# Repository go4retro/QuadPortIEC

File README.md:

# QuadPortIEC
Extremely simple 4 port IEC "extension" port.

This hardly qualifies as a design.  In 2010, Sean Kenny asked if I could design a simple board that allowed him to "disable" some of the drives on the IEC drive bus so he could have multiple devices with the same device number.  The design relies on the fact that an IEC device can be effectively "hidden" by interrupting the ATN line to that device.  

Feel free to use as desired.  Files are in EAGLE CAD format.

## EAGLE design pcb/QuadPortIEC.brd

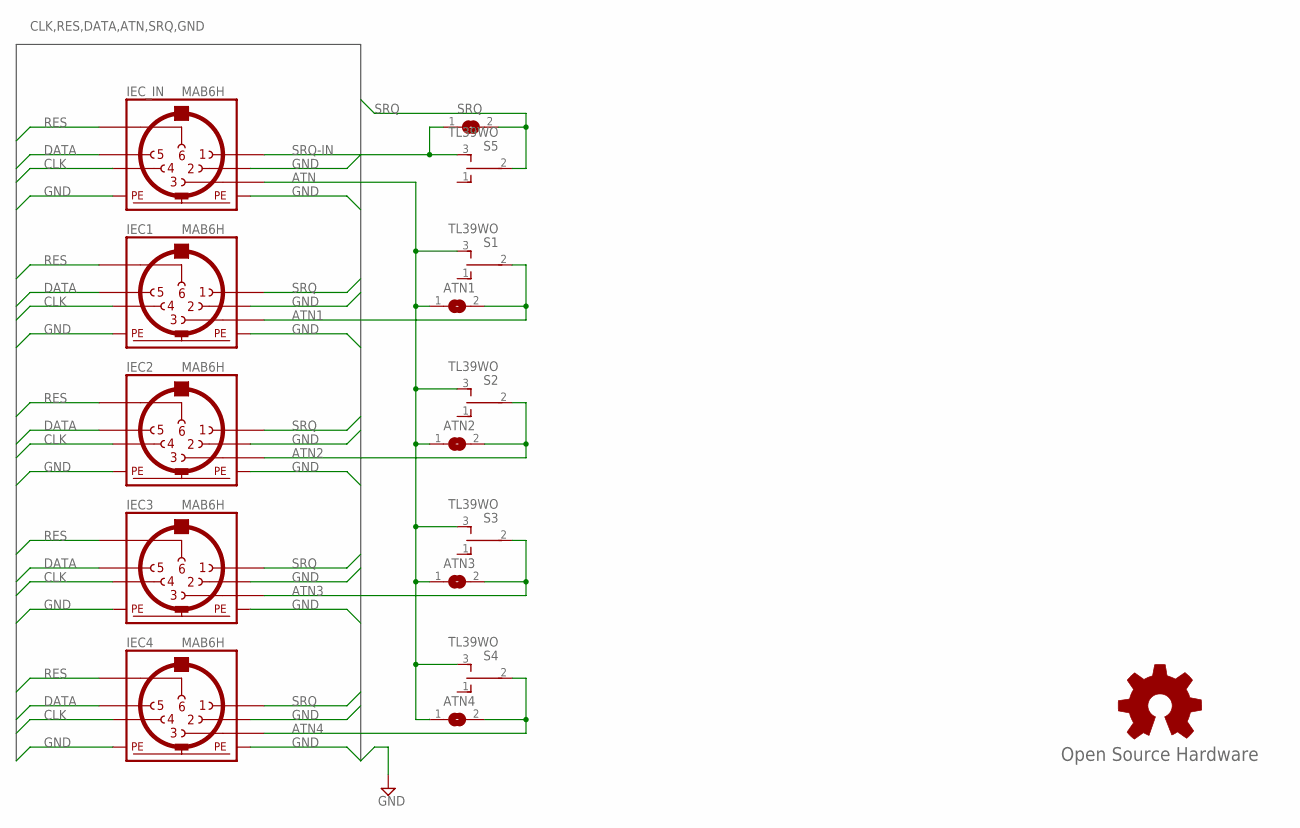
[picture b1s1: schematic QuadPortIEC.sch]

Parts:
ATN1, ATN2, ATN3, ATN4: SJ
GOLD_ORB_SM1: Open Source Hardware; OSHW_8MM
IEC1, IEC2, IEC3, IEC4: MAB6H
IEC_IN: MAB6H
S1, S2, S3, S4, S5: TL39WO; TL3XWO
SRQ: SJ

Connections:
ATN: ATN1.1, ATN2.1, ATN3.1, ATN4.1, IEC_IN.3, S1.3 (S), S2.3 (S), S3.3 (S), S4.3 (S)
ATN1: ATN1.2, IEC1.3, S1.2
ATN2: ATN2.2, IEC2.3, S2.2
ATN3: ATN3.2, IEC3.3, S3.2
ATN4: ATN4.2, IEC4.3, S4.2
CLK: IEC1.4, IEC2.4, IEC3.4, IEC4.4, IEC_IN.4
DATA: IEC1.5, IEC2.5, IEC3.5, IEC4.5, IEC_IN.5
GND: IEC1.2, IEC1.PE, IEC1.PE@ (PE), IEC2.2, IEC2.PE, IEC2.PE@ (PE), IEC3.2, IEC3.PE, IEC3.PE@ (PE), IEC4.2, IEC4.PE, IEC4.PE@ (PE), IEC_IN.2, IEC_IN.PE, IEC_IN.PE@ (PE)
RES: IEC1.6, IEC2.6, IEC3.6, IEC4.6, IEC_IN.6
SRQ: IEC1.1, IEC2.1, IEC3.1, IEC4.1, S5.2, SRQ.2
SRQ-IN: IEC_IN.1, S5.3 (S), SRQ.1

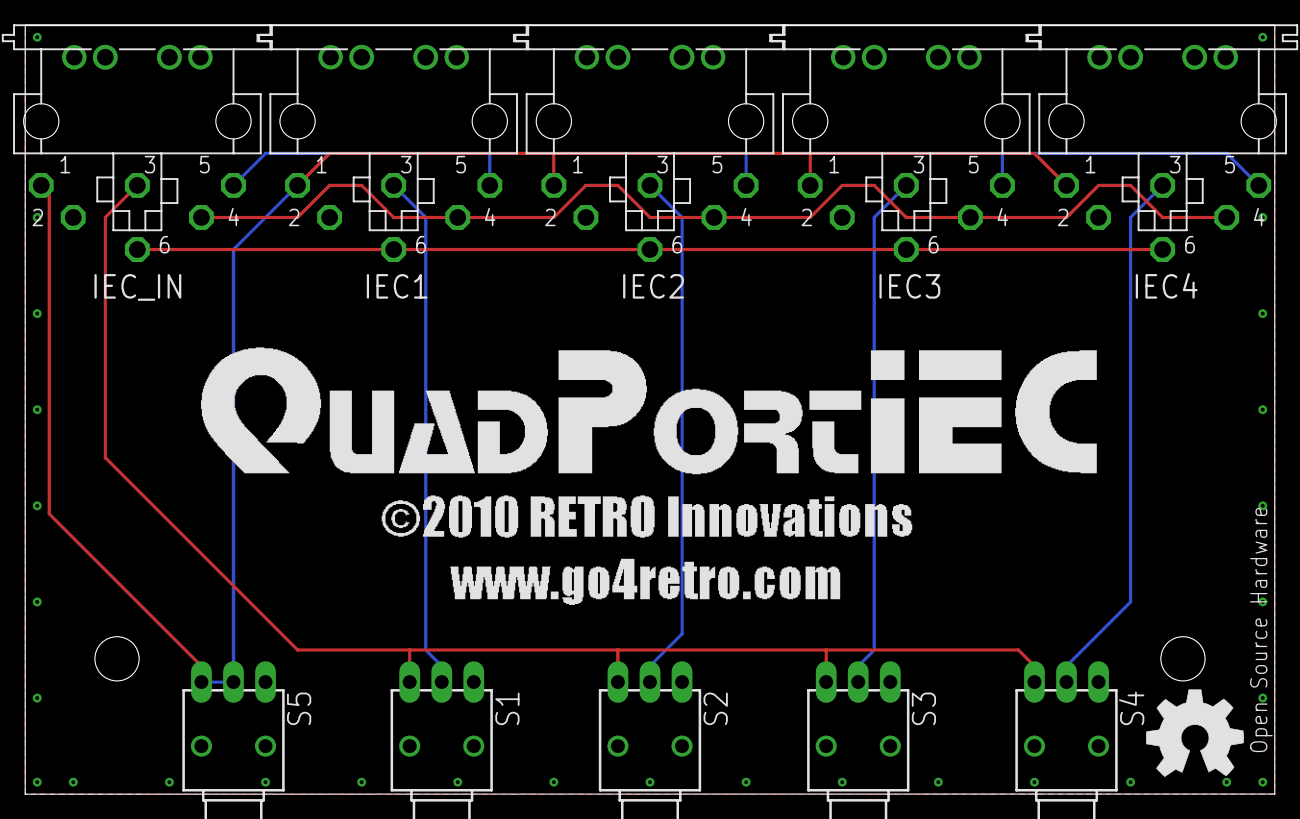
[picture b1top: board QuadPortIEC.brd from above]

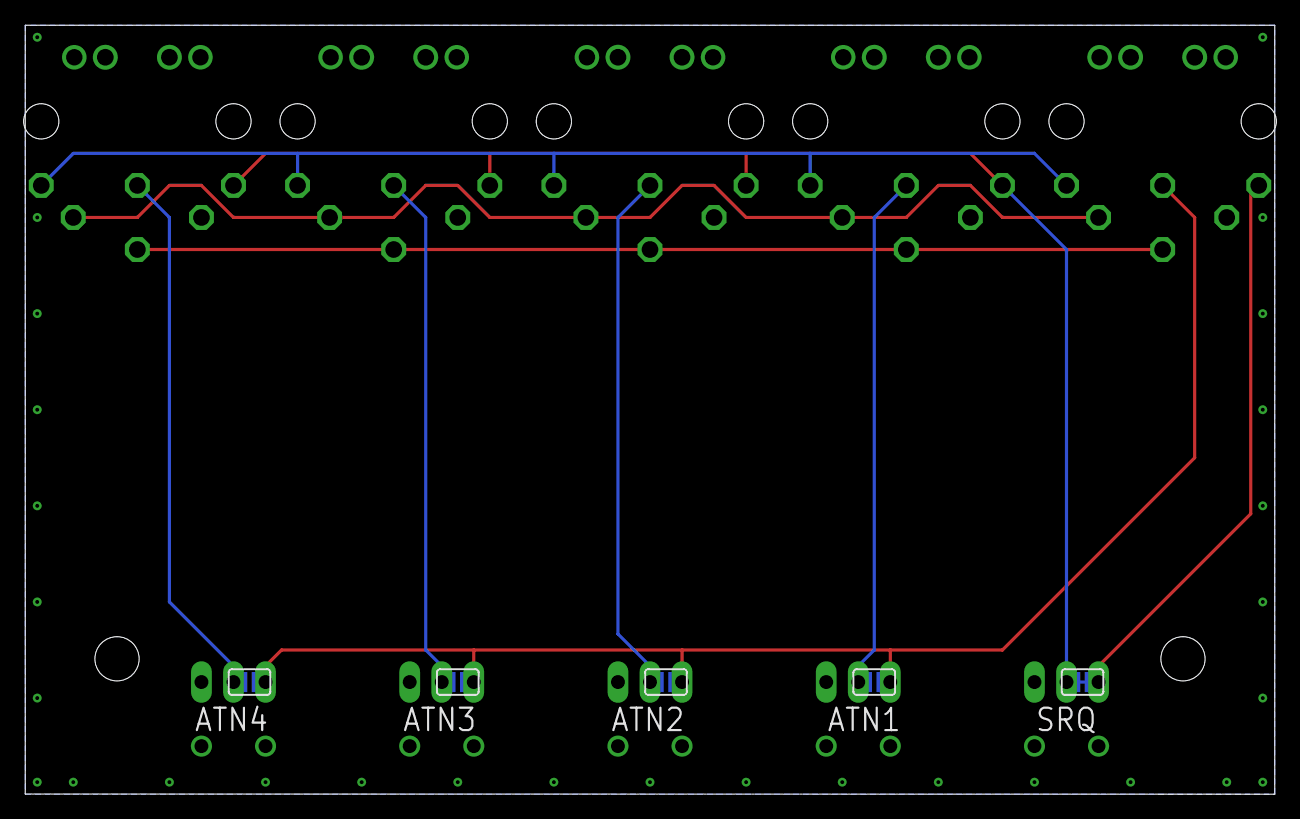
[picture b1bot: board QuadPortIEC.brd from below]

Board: 2 copper layers, 99.1 x 61.0 mm, 16 parts (5 on the bottom side), 11 nets.

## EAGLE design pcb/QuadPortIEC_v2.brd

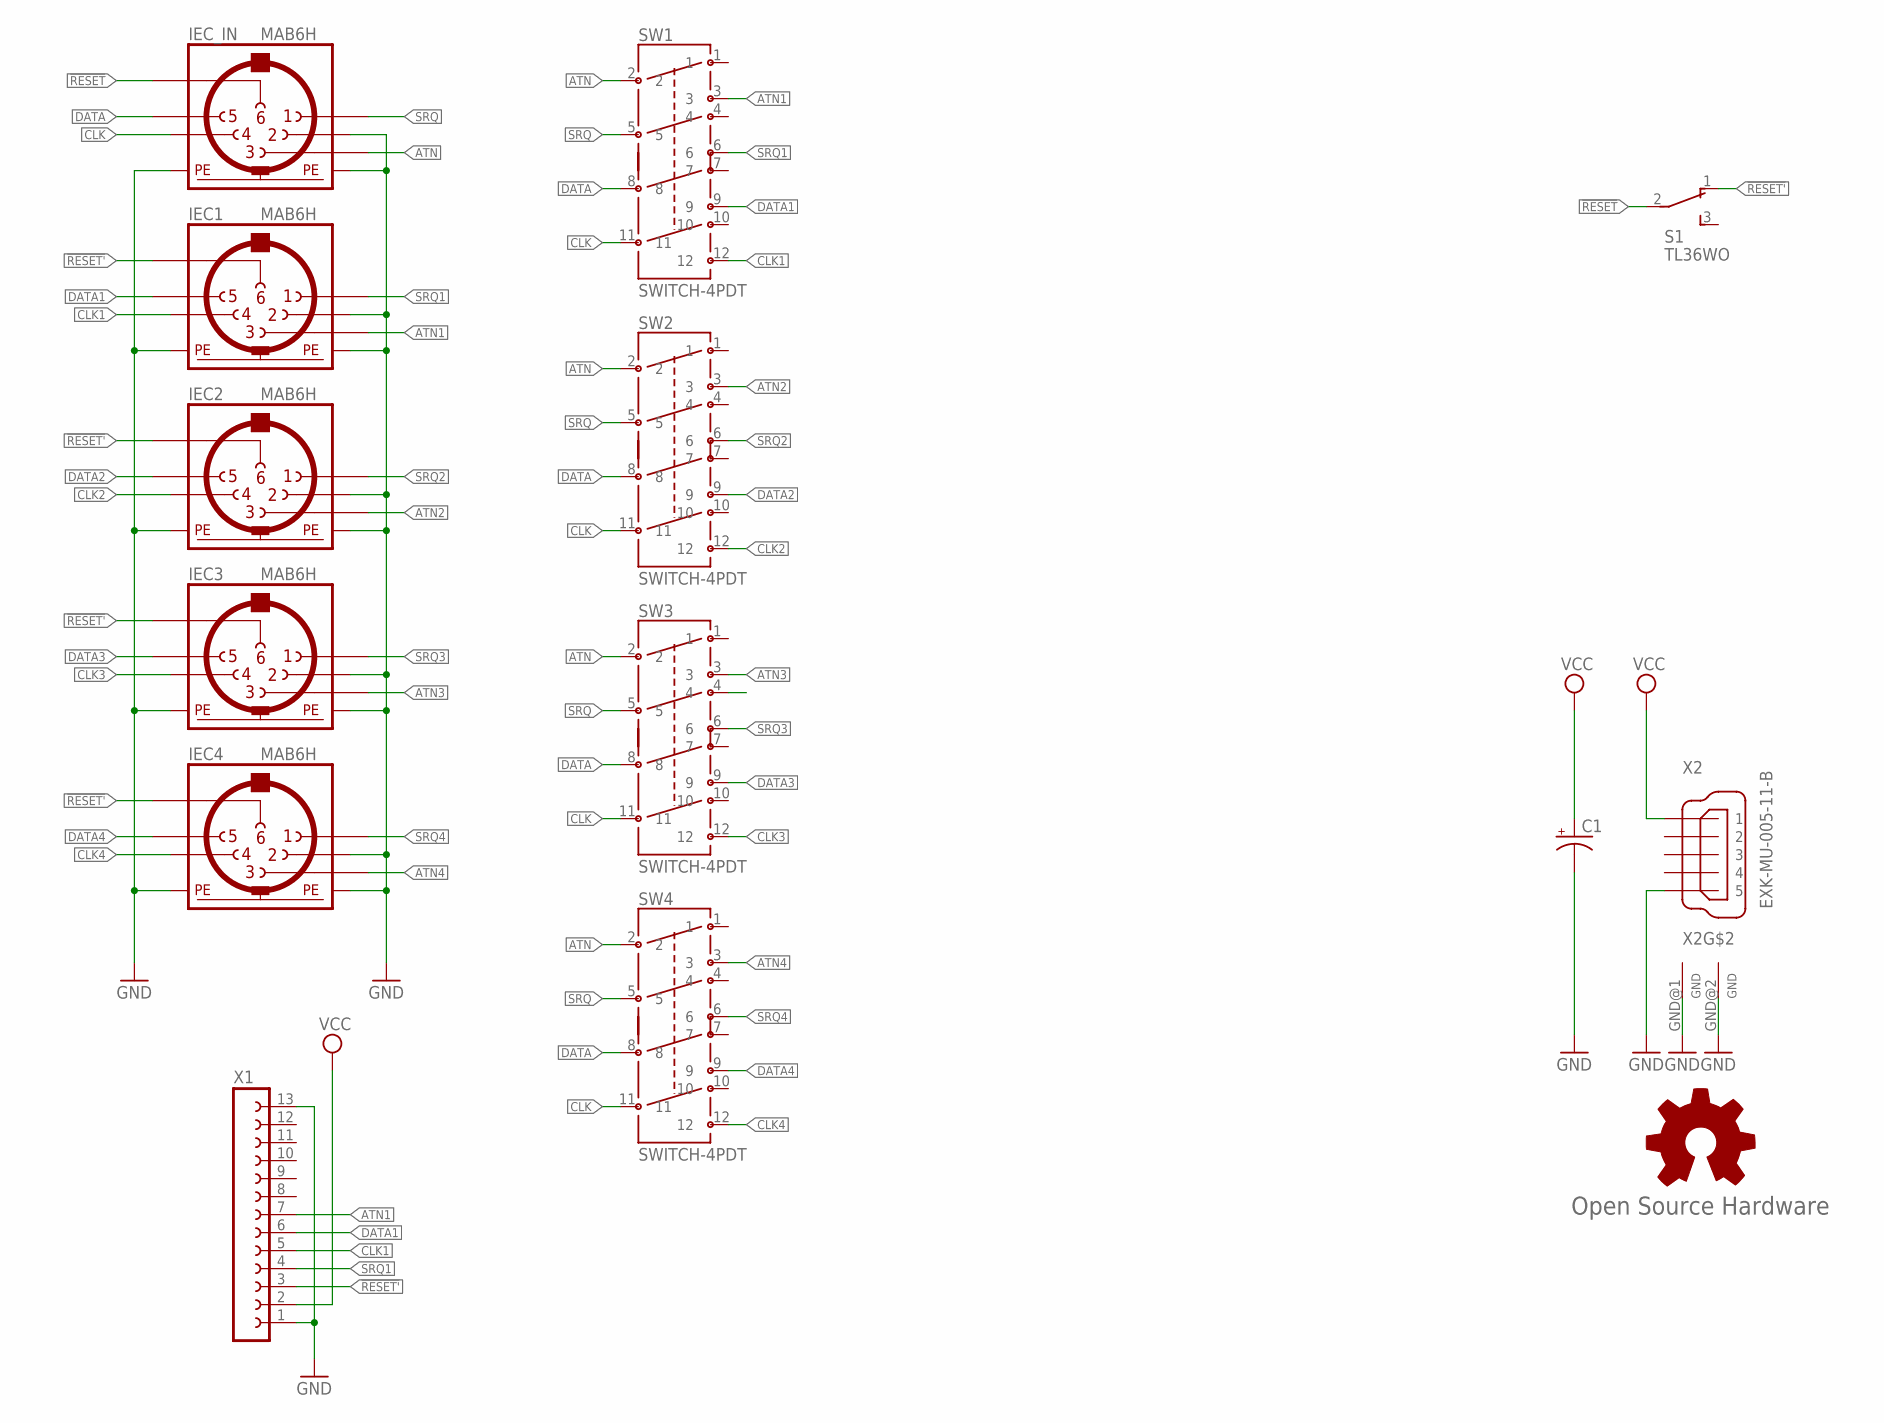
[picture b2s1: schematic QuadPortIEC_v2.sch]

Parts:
C1: CPOL-USE5-8.5; E5-8,5
GOLD_ORB_SM1: Open Source Hardware; OSHW_8MM
IEC1, IEC2, IEC3, IEC4: MAB6H
IEC_IN: MAB6H
S1: TL36WO; TL3XWO
SW1, SW2, SW3, SW4: SWITCH-4PDT; SWITCH-4PDT-ALPS
X1: FE13W
X2: EXK-MU-005-11-B; MINI-USB

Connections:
!RESET: IEC_IN.6, S1.2
!RESET': IEC1.6, IEC2.6, IEC3.6, IEC4.6, S1.1 (O), X1.3
ATN: IEC_IN.3, SW1.2, SW2.2, SW3.2, SW4.2
ATN1: IEC1.3, SW1.3, X1.7
ATN2: IEC2.3, SW2.3
ATN3: IEC3.3, SW3.3
ATN4: IEC4.3, SW4.3
CLK: IEC_IN.4, SW1.11, SW2.11, SW3.11, SW4.11
CLK1: IEC1.4, SW1.12, X1.5
CLK2: IEC2.4, SW2.12
CLK3: IEC3.4, SW3.12
CLK4: IEC4.4, SW4.12
DATA: IEC_IN.5, SW1.8, SW2.8, SW3.8, SW4.8
DATA1: IEC1.5, SW1.9, X1.6
DATA2: IEC2.5, SW2.9
DATA3: IEC3.5, SW3.9
DATA4: IEC4.5, SW4.9
GND: C1.-, IEC1.2, IEC1.PE, IEC1.PE@ (PE), IEC2.2, IEC2.PE, IEC2.PE@ (PE), IEC3.2, IEC3.PE, IEC3.PE@ (PE), IEC4.2, IEC4.PE, IEC4.PE@ (PE), IEC_IN.2, IEC_IN.PE, IEC_IN.PE@ (PE), X1.1, X1.13, X2.GND (5), X2.GND@1 (GND), X2.GND@2 (GND)
SRQ: IEC_IN.1, SW1.5, SW2.5, SW3.5, SW4.5
SRQ1: IEC1.1, SW1.6, X1.4
SRQ2: IEC2.1, SW2.6
SRQ3: IEC3.1, SW3.6
SRQ4: IEC4.1, SW4.6
VCC: C1.+, X1.2, X2.VBUS (1)

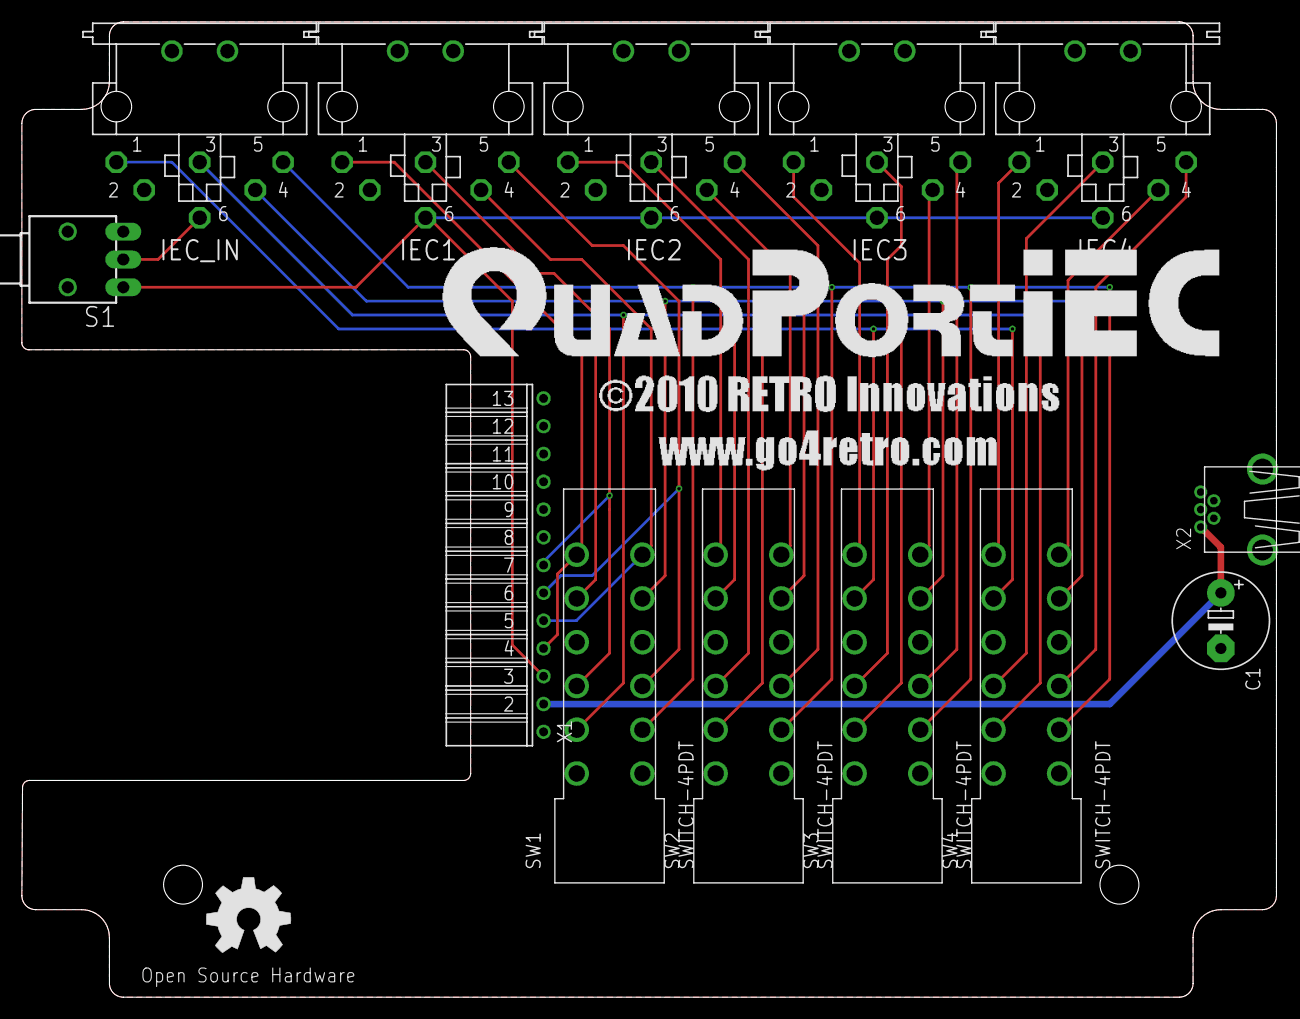
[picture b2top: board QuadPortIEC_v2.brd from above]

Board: 2 copper layers, 114.7 x 89.2 mm, 14 parts (0 on the bottom side), 24 nets.

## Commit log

2019-09-08 Added README.md
2019-09-08 Updated EAGLE files to post 5.x format (XML) and added Open Source Hardware logo to design
2025-06-30 Add in v2
